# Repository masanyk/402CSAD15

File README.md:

# 402CSAD15 — Лабораторна робота №1 (АПКС)

**Студент:** Процак Максим Степанович  
**Група:** КІ-402  
**Варіант:** 15 (JavaScript + npm scripts + Jest)  
**Дисципліна:** Автоматизація проєктування комп'ютерних систем

## Опис проєкту

Кросплатформний JavaScript проєкт Hello World, створений за допомогою AI-агента
`build-engineer`. Агент автоматизує весь процес: від ініціалізації репозиторію
до налаштування CI/CD на трьох операційних системах.

## Структура гілок

| Гілка | Вміст |
|-------|-------|
| `develop` | AI-агент з інструкціями (manifest, skills, commands) |
| `feature/lab1` | Реальний JavaScript проєкт (src, tests, CI workflow) |

## Як запустити AI-агента

Детальні інструкції у [`docs/usage.md`](docs/usage.md).

**Коротко:**
1. Відкрий репозиторій у VS Code
2. Відкрий Copilot Chat (`Ctrl+Alt+I`)
3. Напиши `@workspace /init` або завантаж файл `init.prompt.md`

## Як запустити проєкт локально

```bash
# Встановити залежності
npm install

# Запустити Hello World
npm start

# Запустити тести
npm test

# Зібрати виконуваний файл і запустити його
npm run build
./build/hello/hello        # Windows: buildhellohello.cmd
```

## Документація

- [Архітектура агента](docs/architecture.md)
- [Інструкція запуску](docs/usage.md)
- [Журнал роботи з AI](docs/ai-log.md)

## CI/CD

GitHub Actions автоматично запускає збірку і тести при кожному push до `develop`.

Перевіряються три операційні системи:
- ✅ Ubuntu (Linux)
- ✅ Windows
- ✅ macOS

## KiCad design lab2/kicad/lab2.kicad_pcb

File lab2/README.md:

# ЛР2 АПКС — проєктування та топологія друкованої плати

**Студент:** Процак Максим Степанович, КІ-402, варіант 15
**GUID:** `026d6220-80f6-5b5d-ac5d-0a5dfb622ab7` (UUID v5 від ПІБ, `scripts/design.py`)
**САПР:** KiCad 10.0.8, автотрасування — Freerouting 2.1.0

## Що де лежить

| Шлях | Вміст |
|------|-------|
| `АПКС_Процак_Ki-402_lab2.docx` / `.pdf` | звіт |
| `kicad/lab2.kicad_pro` | проєкт KiCad (відкрити двоклацом) |
| `kicad/lab2.kicad_sch` | принципова схема |
| `kicad/lab2.kicad_pcb` | плата 85.6 × 53.98 мм, розведена |
| `kicad/lab2.kicad_sym`, `kicad/lab2.pretty/` | символи та футпринти U1–U5, J1 |
| `kicad/drc.rpt`, `kicad/erc.rpt` | звіти DRC / ERC (0 помилок) |
| `gerber/`, `lab2_gerber.zip` | Gerber RS-274X + свердління Excellon |
| `img/` | зображення схеми й плати для звіту |
| `scripts/` | генератори: усе відтворюється однією командою |

## Відтворення

```bash
bash scripts/build.sh
```

Кроки: GUID і таблиця з'єднань → бібліотека та схема → ERC → плата і DSN →
Freerouting → імпорт трас → DRC з перевіркою відповідності схемі → Gerber → зображення → звіт.

Шляхи до KiCad і Freerouting задаються змінними `KICAD` і `FREEROUTING`
(за замовчуванням `%LOCALAPPDATA%\Programs\KiCad\10.0\bin` і `C:\Users\maksp\tools\freerouting\freerouting-2.1.0.jar`).
Freerouting 2.1.0 обрано, бо новіші версії потребують Java 25, а встановлена Java 21.

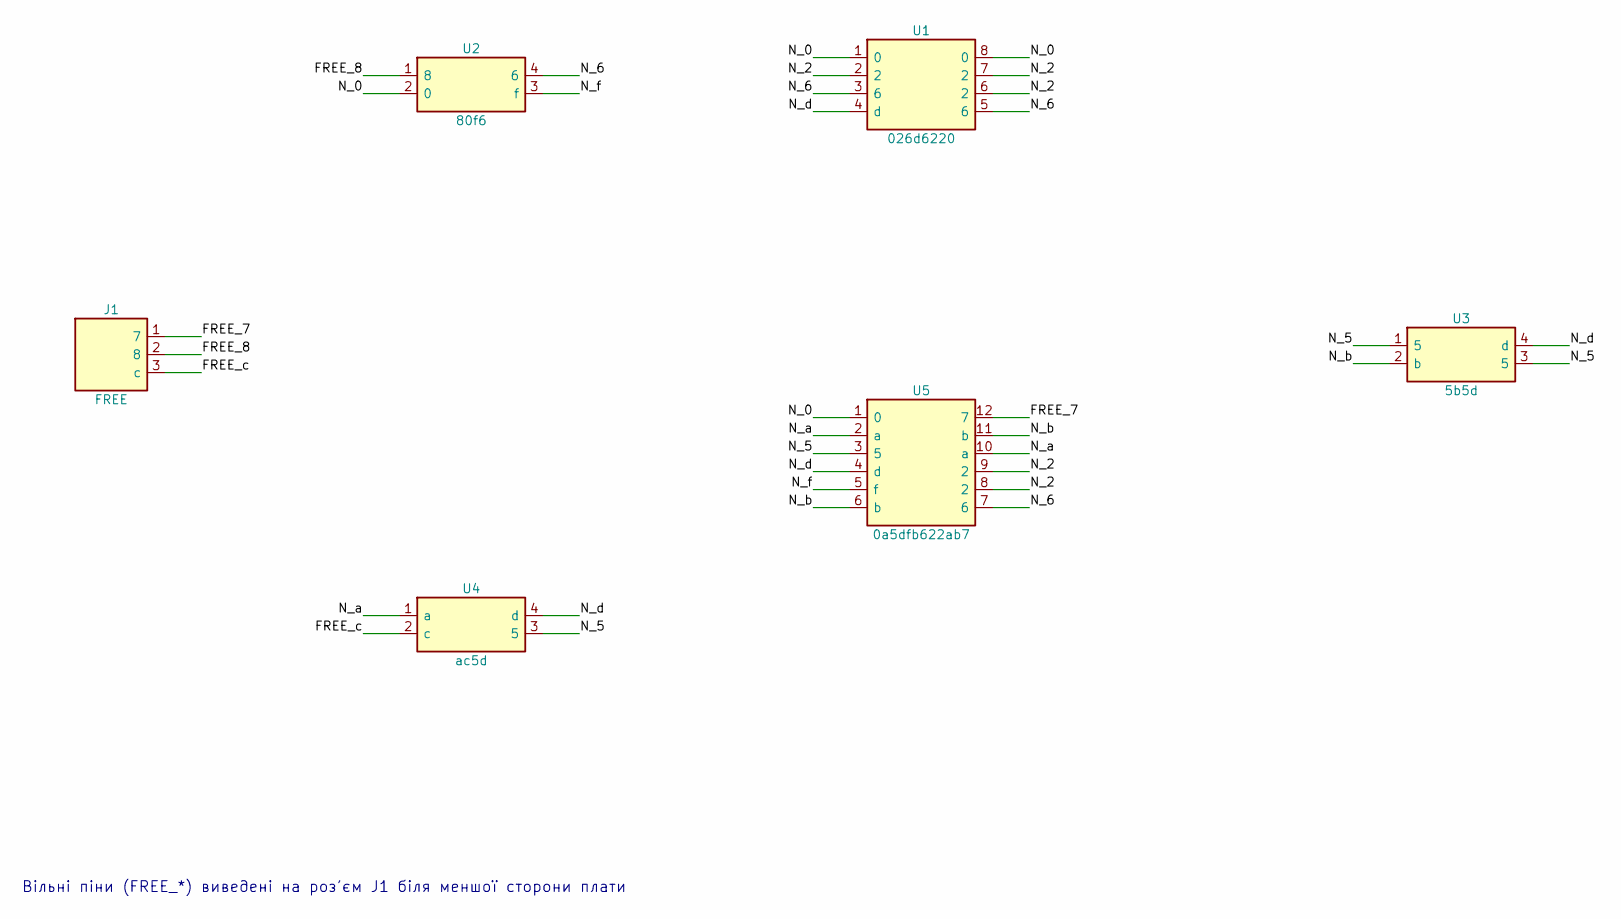
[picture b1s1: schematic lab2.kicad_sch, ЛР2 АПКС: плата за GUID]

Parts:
J1: FREE; CONN3
U1: 026d6220; SQ8
U2: 80f6; SQ4
U3: 5b5d; SQ4
U4: ac5d; SQ4
U5: 0a5dfb622ab7; SQ12

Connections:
/FREE_7: J1.1 (7), U5.12 (7)
/FREE_8: J1.2 (8), U2.1 (8)
/FREE_c: J1.3 (c), U4.2 (c)
/N_0: U1.1 (0), U1.8 (0), U2.2 (0), U5.1 (0)
/N_2: U1.2, U1.6 (2), U1.7 (2), U5.8 (2), U5.9 (2)
/N_5: U3.1 (5), U3.3 (5), U4.3 (5), U5.3 (5)
/N_6: U1.3 (6), U1.5 (6), U2.4 (6), U5.7 (6)
/N_a: U4.1 (a), U5.2 (a), U5.10 (a)
/N_b: U3.2 (b), U5.6 (b), U5.11 (b)
/N_d: U1.4 (d), U3.4 (d), U4.4 (d), U5.4 (d)
/N_f: U2.3 (f), U5.5 (f)

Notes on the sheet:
Вільні піни (FREE_*) виведені на роз'єм J1 біля меншої сторони плати

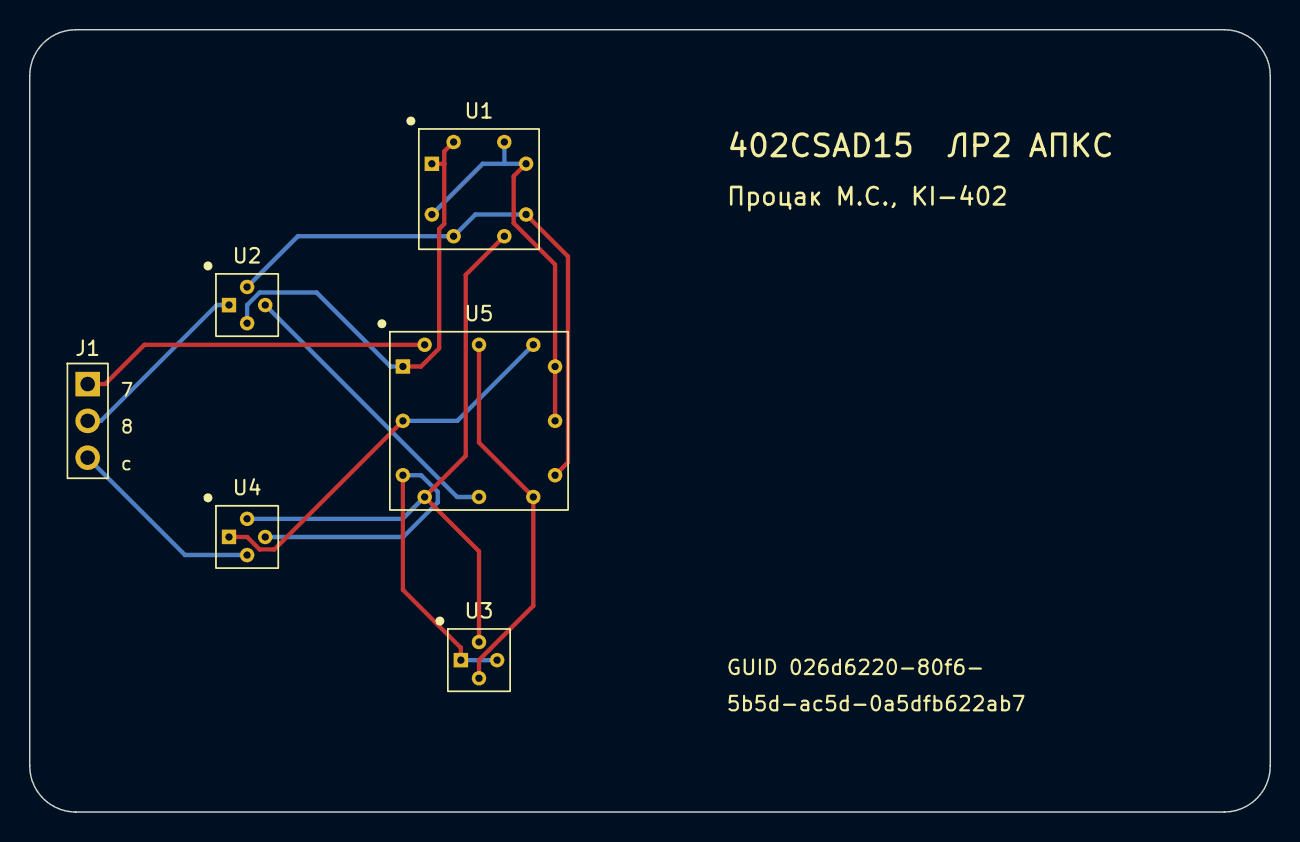
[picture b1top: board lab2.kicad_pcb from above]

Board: 2 copper layers, 85.6 x 54.0 mm, 6 parts (0 on the bottom side), 11 nets.
